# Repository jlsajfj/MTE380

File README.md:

# MTE380
STM32 Programming with NUCLEO-F401RE Board

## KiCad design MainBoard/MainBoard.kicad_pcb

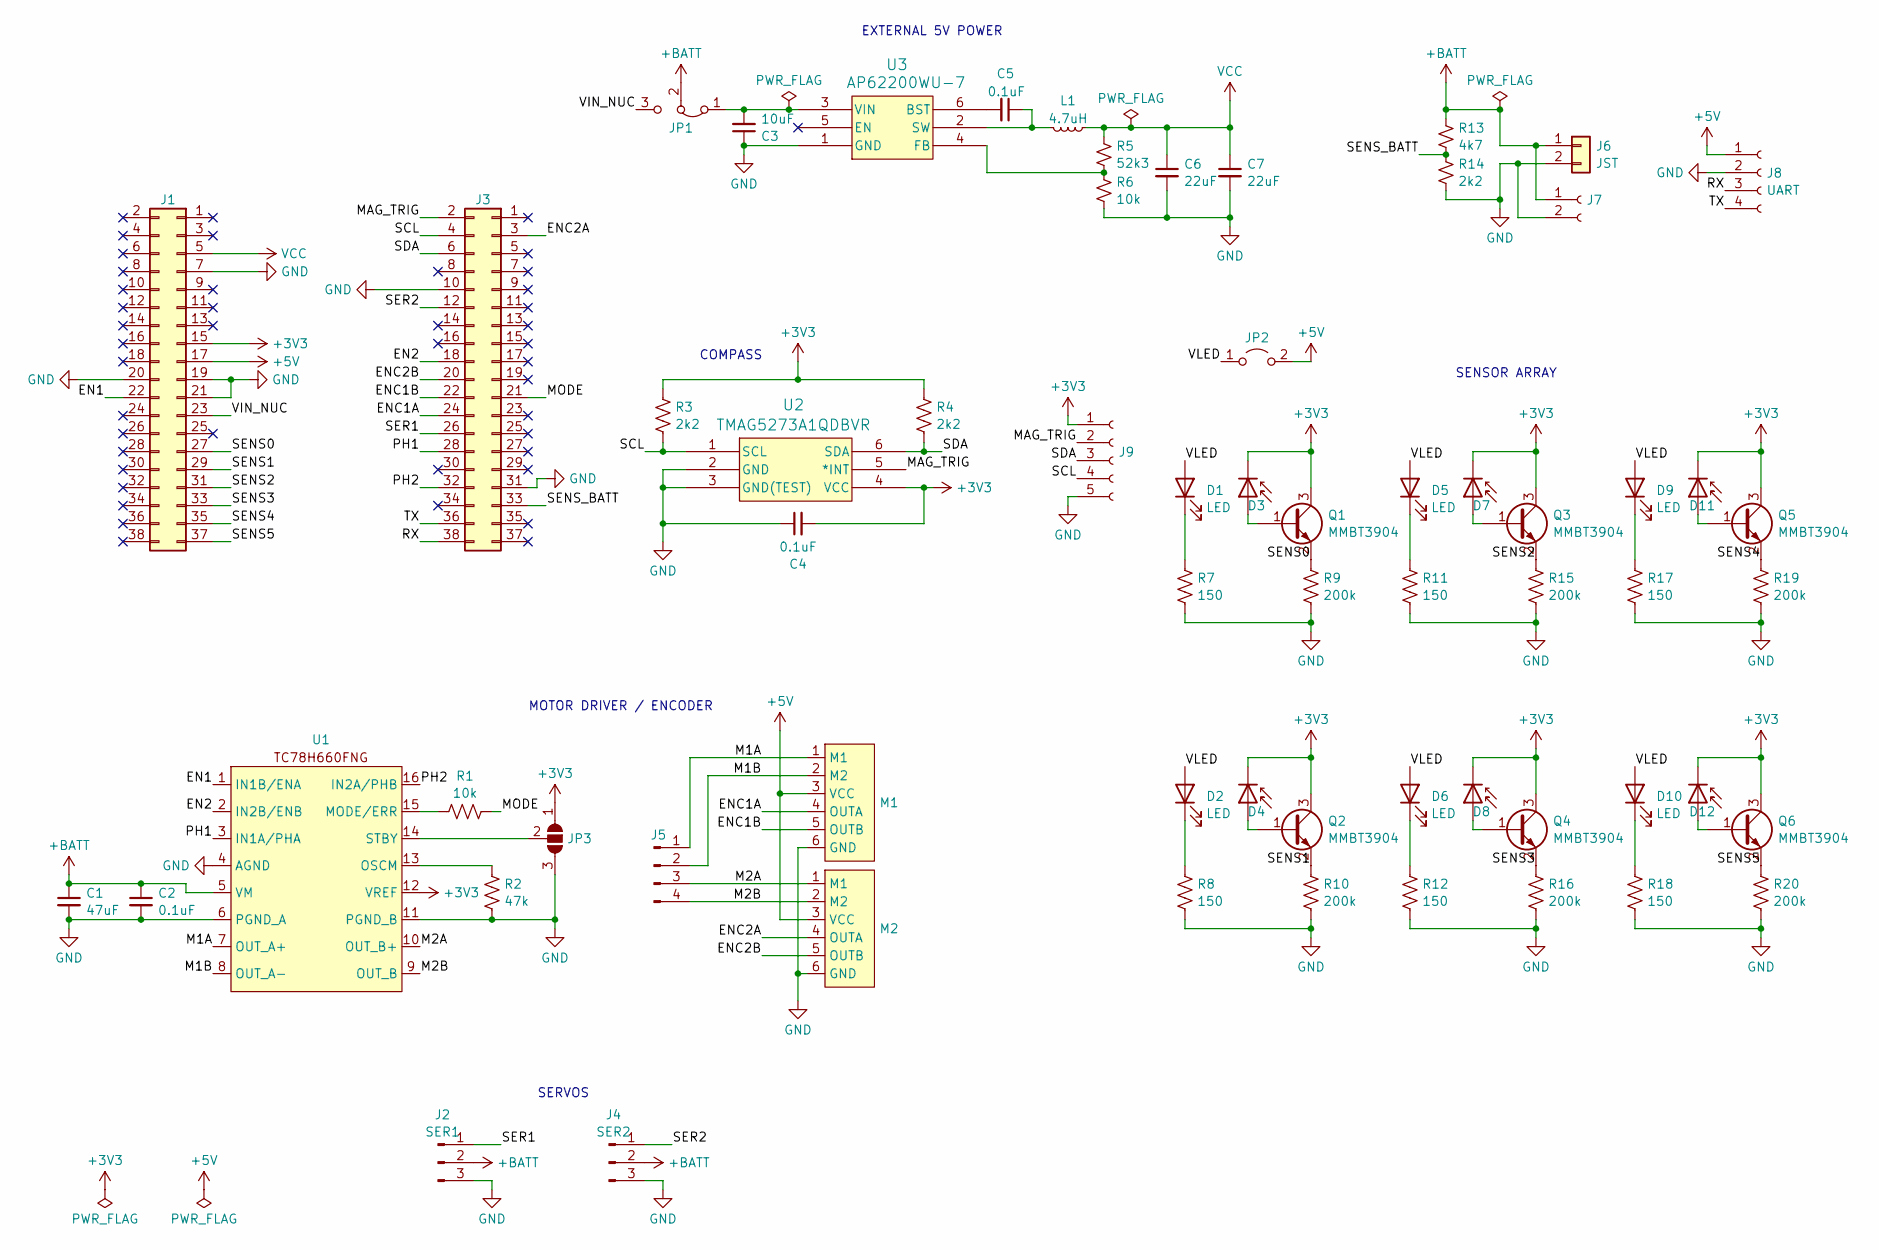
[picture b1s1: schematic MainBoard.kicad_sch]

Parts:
C1: 47uF; C_Radial_D5.0mm_H7.0mm_P2.00mm
C2, C4, C5: 0.1uF; C_0805_2012Metric_Pad1.18x1.45mm_HandSolder
C3: 10uF; C_0805_2012Metric_Pad1.18x1.45mm_HandSolder
C6, C7: 22uF; C_0805_2012Metric_Pad1.18x1.45mm_HandSolder
D1, D2, D5, D6, D9, D10: LED; LED_D3.0mm
D3, D4, D7, D8, D11, D12: D_Photo; LED_D5.0mm
J1, J3: Conn_02x19_Odd_Even; PinSocket_2x19_P2.54mm_Vertical
J2: SER1; PinHeader_1x03_P2.54mm_Vertical
J4: SER2; PinHeader_1x03_P2.54mm_Vertical
J5: Conn_01x04_Pin; PinHeader_1x04_P2.54mm_Horizontal
J6: JST; JST_PH_B2B-PH-K_1x02_P2.00mm_Vertical
J7: Conn_01x02_Socket; PinSocket_1x02_P2.54mm_Vertical
J8: UART; PinSocket_1x04_P2.54mm_Vertical
J9: Conn_01x05_Socket; PinHeader_1x05_P2.54mm_Vertical
JP1: Jumper_3_Bridged12; PinHeader_1x03_P2.54mm_Vertical
JP2: Jumper_2_Open; PinHeader_1x02_P2.54mm_Vertical
JP3: SolderJumper_3_Bridged12; SolderJumper-3_P2.0mm_Open_TrianglePad1.0x1.5mm
L1: 4.7uH; L_0805_2012Metric_Pad1.15x1.40mm_HandSolder
M1, M2: N20
Q1, Q2, Q3, Q4, Q5, Q6: MMBT3904; SOT-23_Handsoldering
R1, R6: 10k; R_0805_2012Metric_Pad1.20x1.40mm_HandSolder
R2: 47k; R_0805_2012Metric_Pad1.20x1.40mm_HandSolder
R3, R4, R14: 2k2; R_0805_2012Metric_Pad1.20x1.40mm_HandSolder
R5: 52k3; R_0805_2012Metric_Pad1.20x1.40mm_HandSolder
R7, R8, R11, R12, R17, R18: 150; R_0805_2012Metric_Pad1.20x1.40mm_HandSolder
R9, R10, R15, R16, R19, R20: 200k; R_0805_2012Metric_Pad1.20x1.40mm_HandSolder
R13: 4k7; R_0805_2012Metric_Pad1.20x1.40mm_HandSolder
U1: TSSOP-16_4.4x5mm_P0.65mm
U2: TMAG5273A1QDBVR; TSOT-23-6_HandSoldering
U3: AP62200WU-7; TSOT-23-6_HandSoldering

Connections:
+3V3: C4.2, D3.1 (K), D4.1 (K), D7.1 (K), D8.1 (K), D11.1 (K), D12.1 (K), J1.15, J9.1, JP3.1 (A), Q1.3 (C), Q2.3 (C), Q3.3 (C), Q4.3 (C), Q5.3 (C), Q6.3 (C), R3.1, R4.1, U1.12 (VREF), U2.4 (VCC)
+5V: J1.17, J8.1, JP2.2 (B), M1.3 (VCC), M2.3 (VCC)
+BATT: C1.1, C2.1, J2.2, J4.2, J6.1, J7.1, JP1.2 (C), R13.1, U1.5 (VM)
/EN1: J1.22, U1.1 (IN1B/ENA)
/EN2: J3.18, U1.2 (IN2B/ENB)
/ENC1A: J3.24, M1.4 (OUTA)
/ENC1B: J3.22, M1.5 (OUTB)
/ENC2A: J3.3, M2.4 (OUTA)
/ENC2B: J3.20, M2.5 (OUTB)
/M1A: J5.1, M1.1 (M1), U1.7 (OUT_A+)
/M1B: J5.2, M1.2 (M2), U1.8 (OUT_A-)
/M2A: J5.3, M2.1 (M1), U1.10 (OUT_B+)
/M2B: J5.4, M2.2 (M2), U1.9 (OUT_B)
/MAG_TRIG: J3.2, J9.2, U2.5 (*INT)
/MODE: J3.21, R1.2
/PH1: J3.28, U1.3 (IN1A/PHA)
/PH2: J3.32, U1.16 (IN2A/PHB)
/RX: J3.38, J8.3
/SCL: J3.4, J9.4, R3.2, U2.1 (SCL)
/SDA: J3.6, J9.3, R4.2, U2.6 (SDA)
/SENS0: J1.27, Q1.2 (E), R9.1
/SENS1: J1.29, Q2.2 (E), R10.1
/SENS2: J1.31, Q3.2 (E), R15.1
/SENS3: J1.33, Q4.2 (E), R16.1
/SENS4: J1.35, Q5.2 (E), R19.1
/SENS5: J1.37, Q6.2 (E), R20.1
/SENS_BATT: J3.33, R13.2, R14.1
/SER1: J2.1, J3.26
/SER2: J3.12, J4.1
/TX: J3.36, J8.4
/VIN_NUC: J1.23, JP1.3 (B)
/VLED: D1.2 (A), D2.2 (A), D5.2 (A), D6.2 (A), D9.2 (A), D10.2 (A), JP2.1 (A)
GND: C1.2, C2.2, C3.1, C4.1, C6.2, C7.2, J1.7, J1.19, J1.20, J1.21, J2.3, J3.10, J3.31, J4.3, J6.2, J7.2, J8.2, J9.5, JP3.3 (B), M1.6 (GND), M2.6 (GND), R2.2, R6.2, R7.2, R8.2, R9.2, R10.2, R11.2, R12.2, R14.2, R15.2, R16.2, R17.2, R18.2, R19.2, R20.2, U1.4 (AGND), U1.6 (PGND_A), U1.11 (PGND_B), U2.2 (GND), U2.3 (GND(TEST)), U3.1 (GND)
unnamed: D1.1 (K), R7.1
unnamed: D2.1 (K), R8.1
unnamed: D3.2 (A), Q1.1 (B)
unnamed: D4.2 (A), Q2.1 (B)
unnamed: D5.1 (K), R11.1
unnamed: D6.1 (K), R12.1
unnamed: D7.2 (A), Q3.1 (B)
unnamed: D8.2 (A), Q4.1 (B)
unnamed: D9.1 (K), R17.1
unnamed: D10.1 (K), R18.1
unnamed: D11.2 (A), Q5.1 (B)
unnamed: D12.2 (A), Q6.1 (B)
unnamed: C3.2, JP1.1 (A), U3.3 (VIN)
unnamed: JP3.2 (C), U1.14 (STBY)
unnamed: R1.1, U1.15 (MODE/ERR)
unnamed: R2.1, U1.13 (OSCM)
unnamed: C5.2, U3.6 (BST)
unnamed: R5.2, R6.1, U3.4 (FB)
unnamed: C5.1, L1.1, U3.2 (SW)
VCC: C6.1, C7.1, J1.5, L1.2, R5.1

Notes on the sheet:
COMPASS
EXTERNAL 5V POWER
SERVOS
MOTOR DRIVER / ENCODER
SENSOR ARRAY

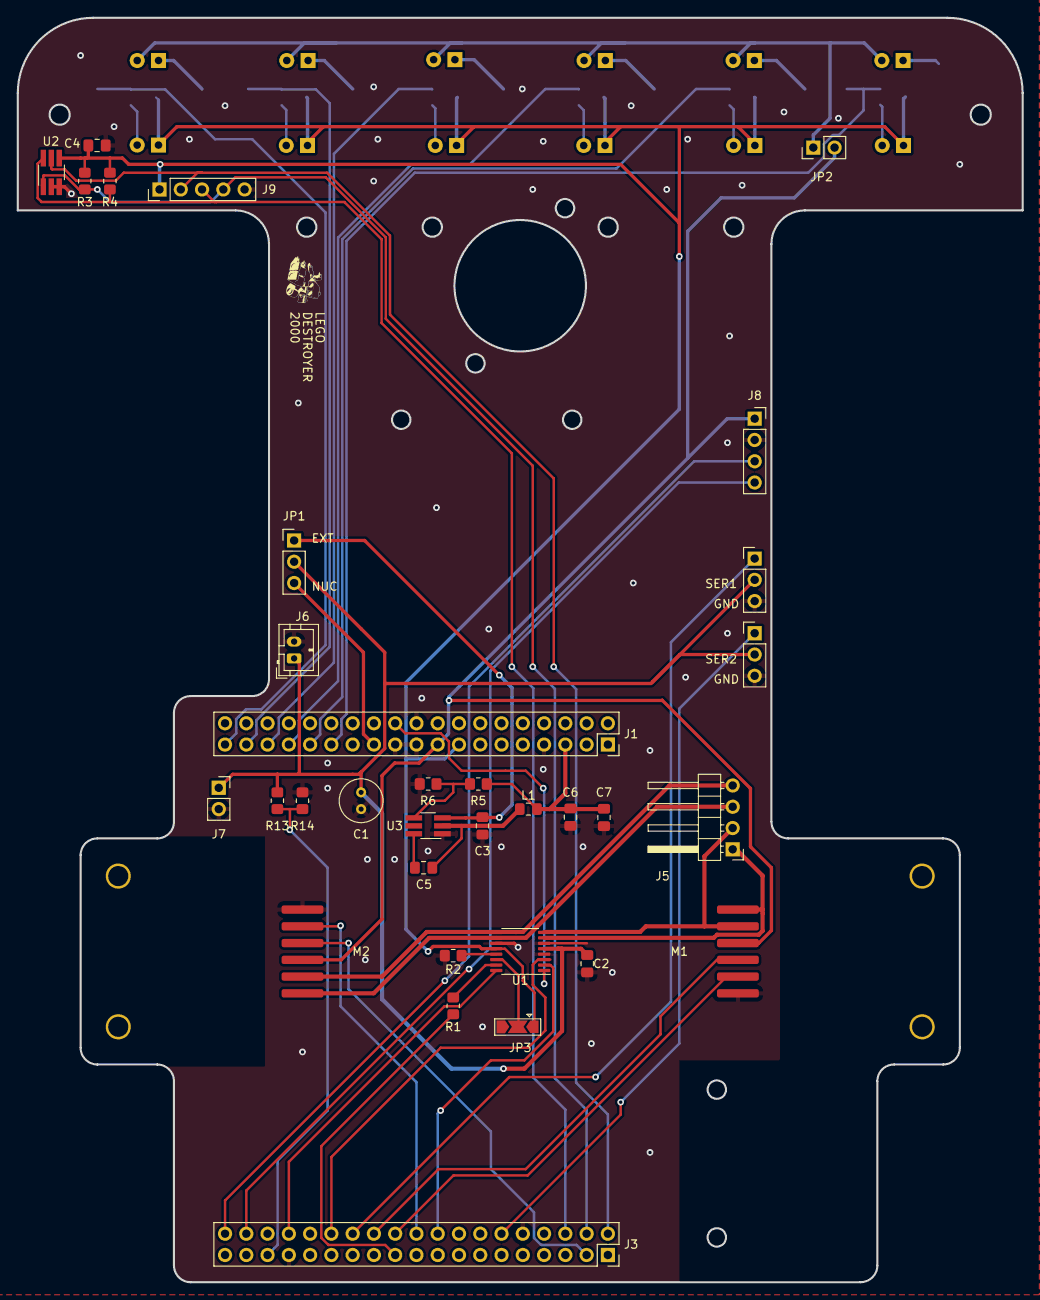
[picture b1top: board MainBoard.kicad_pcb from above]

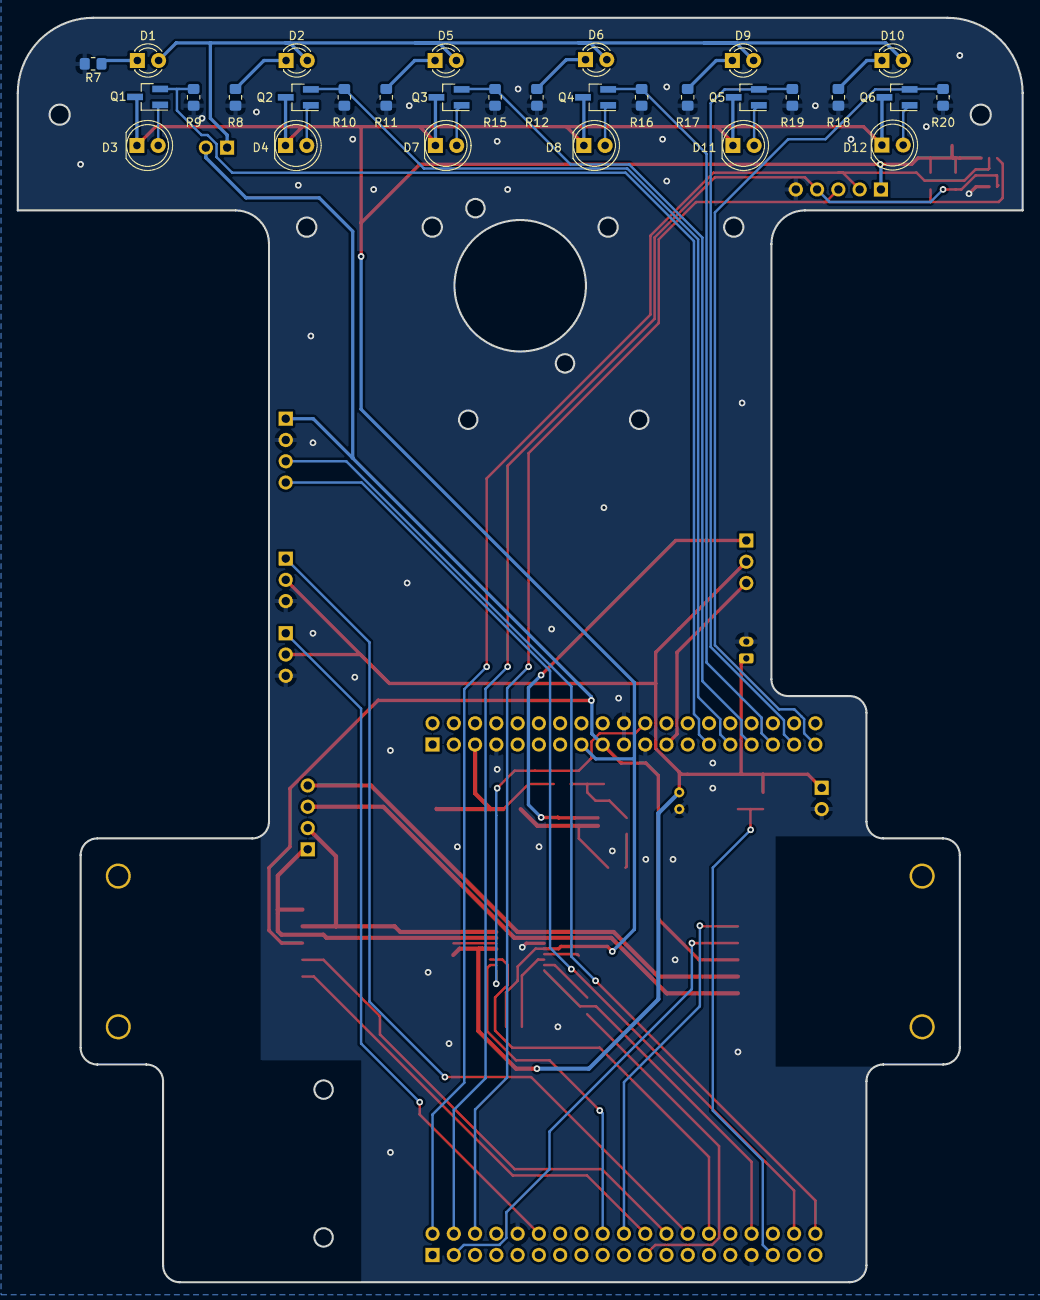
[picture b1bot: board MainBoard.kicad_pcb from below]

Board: 2 copper layers, 120.0 x 151.0 mm, 63 parts (30 on the bottom side), 53 nets.

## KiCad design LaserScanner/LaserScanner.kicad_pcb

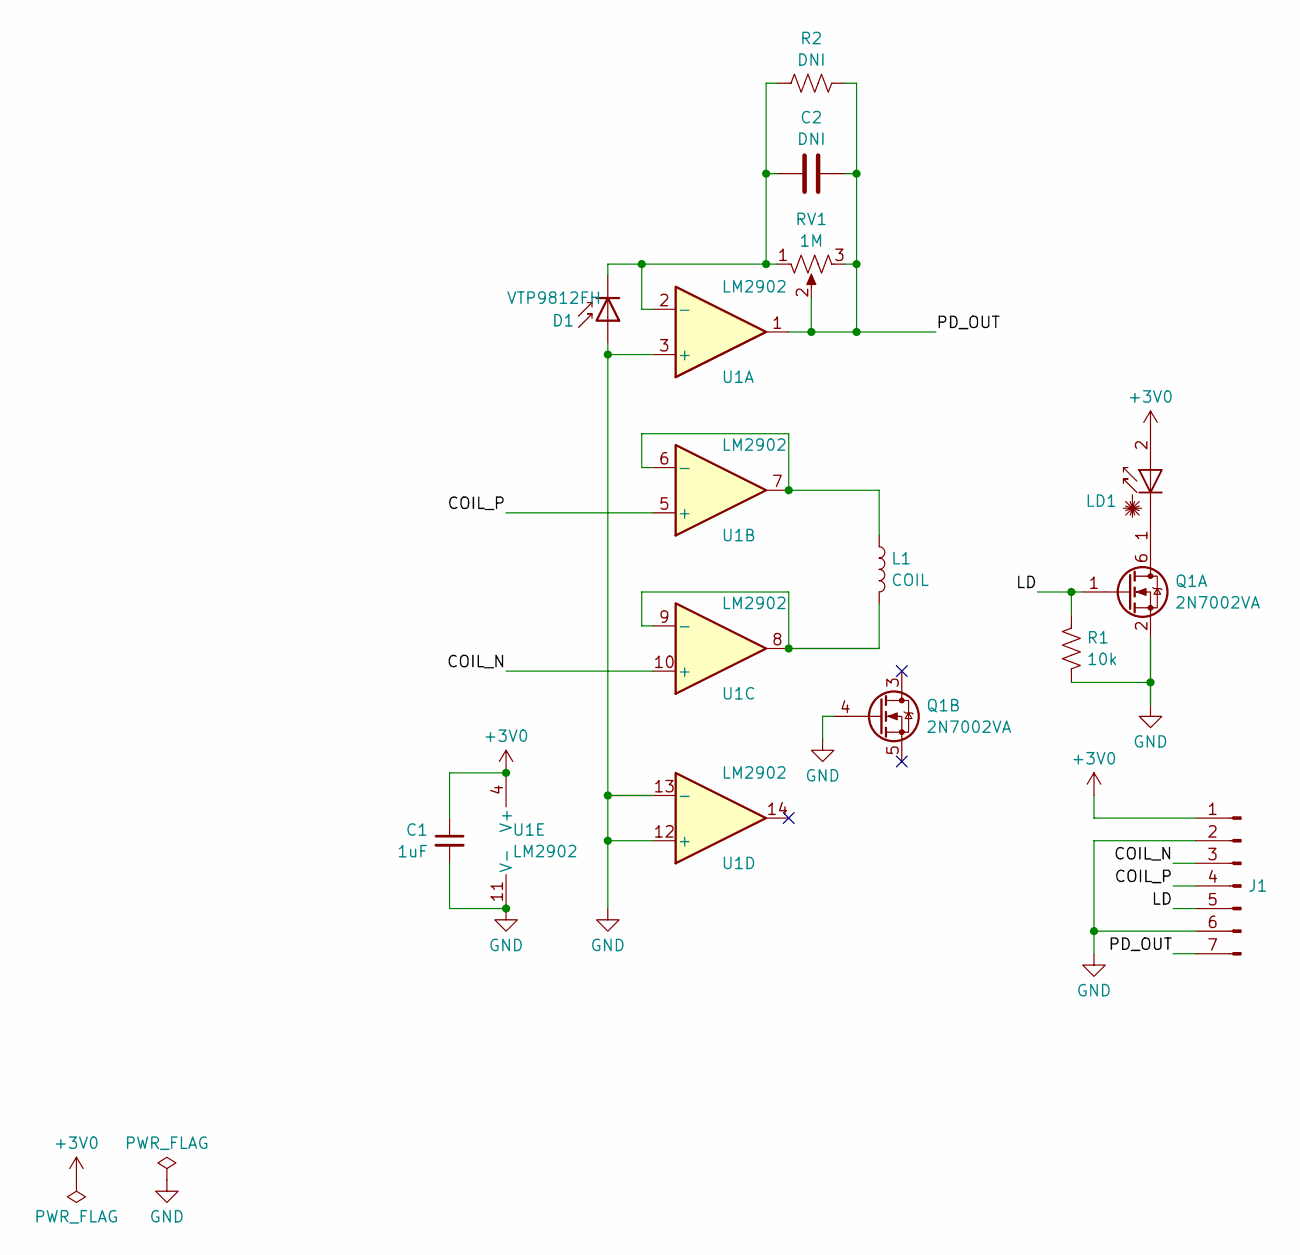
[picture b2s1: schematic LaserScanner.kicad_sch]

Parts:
C1: 1uF; C_0603_1608Metric_Pad1.08x0.95mm_HandSolder
C2: DNI; C_0603_1608Metric_Pad1.08x0.95mm_HandSolder
D1: VTP9812FH; SOD-70_P2.54mm
J1: Conn_01x06_Pin; PinHeader_1x07_P2.54mm_Horizontal
L1: COIL; PinHeader_1x02_P2.54mm_Vertical
LD1: PinHeader_1x02_P2.54mm_Vertical
Q1: 2N7002VA; SOT-23-6_Handsoldering
R1: 10k; R_0603_1608Metric_Pad0.98x0.95mm_HandSolder
R2: DNI; R_0603_1608Metric_Pad0.98x0.95mm_HandSolder
RV1: 1M; Potentiometer_Bourns_3296W_Vertical
U1: LM2902; SOIC127P600X175-14N

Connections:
+3V0: C1.1, J1.1, LD1.2 (A), U1.4 (V+)
/COIL_N: J1.3, U1.10 (+)
/COIL_P: J1.4, U1.5 (+)
/LD: J1.5, Q1.1 (G), R1.1
/PD_OUT: C2.2, J1.7, R2.2, RV1.2, RV1.3, U1.1
GND: C1.2, D1.2 (A), J1.2, J1.6, Q1.2 (S), Q1.4 (G), R1.2, U1.3 (+), U1.11 (V-), U1.12 (+), U1.13 (-)
unnamed: C2.1, D1.1 (K), R2.1, RV1.1, U1.2 (-)
unnamed: LD1.1 (K), Q1.6 (D)
unnamed: L1.1, U1.6 (-), U1.7
unnamed: L1.2, U1.8, U1.9 (-)

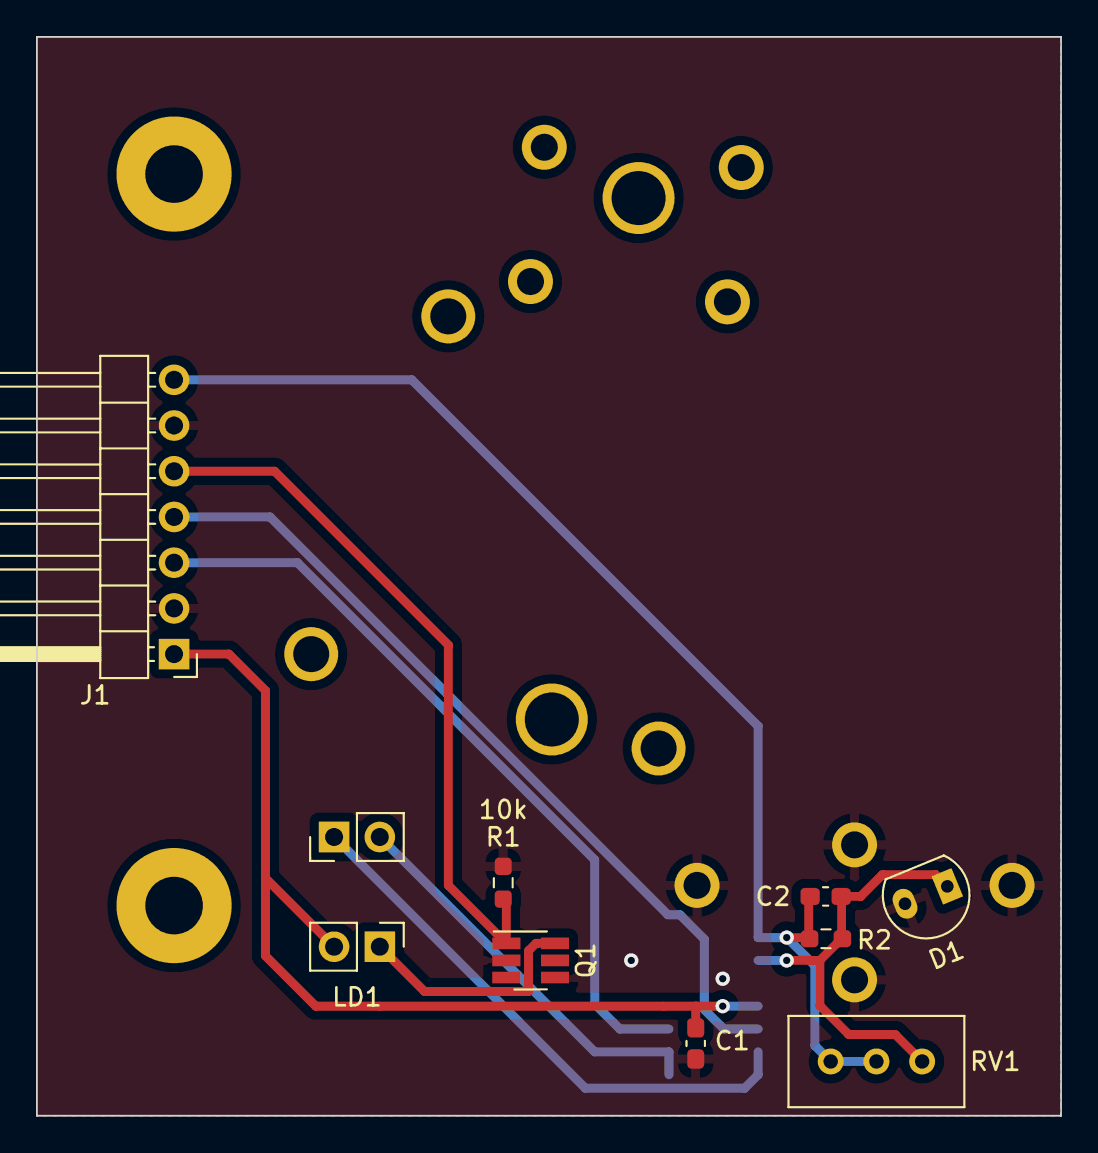
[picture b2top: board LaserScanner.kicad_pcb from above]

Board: 2 copper layers, 56.9 x 59.9 mm, 11 parts (1 on the bottom side), 10 nets.

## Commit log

2024-01-15 Project Creation
    Created Project with Nucleo-F401RE Board
2024-01-19 Motor driver first push
2024-01-20 gitignore cleanup
2024-01-20 add platformio config
2024-01-20 motor test code
2024-01-21 Motor Driver getFault and setEnabled functions
2024-01-26 adc code
2024-01-28 first line following code
2024-01-29 calibration, command system, config
2024-01-29 move more parameters to config framework
2024-01-29 make motor speed a config
2024-02-02 make sensor gains symmetric
2024-02-02 laser scanner circuit files
2024-02-02 limit speed in controller
2024-02-11 add pid controller
2024-02-11 Update Motor PWM
    change tim2 and tim3 pre-scalers. changed pre-scaler from 84 to 2, changed auto reload register from 100 to 1024
2024-02-11 Start Servo Code
    started some servo code, will need help to finish the firmware, need to add start and stop limits to command
2024-02-12 Bunch of Changes
    Updated Baud rate to 9600, created servo toggle and all other related functions
2024-02-13 experimental turn around and add servo support in commands
2024-02-15 add encoder support
2024-02-16 add pid for motor speed and position
2024-02-16 have pid_reset caller keep track of last output
2024-02-16 add interface to get motor count
2024-02-19 add compass support
2024-02-23 main board schematics
2024-02-23 add external 5V regulator
2024-02-24 use dma for serial printing
2024-02-24 bump uart rate and handle burst transmission better
2024-02-26 mainboard layout
2024-02-27 routing
2024-02-27 add logo
2024-02-27 update routing
2024-03-01 fix motor pid usage
2024-03-01 poc pid tuning tool
2024-03-06 update to new board
2024-03-07 add lowpass to compass calibration; add demo code
2024-03-08 add multi servo support
2024-03-10 battery voltage; add idle mode to compass
2024-03-12 elliptic curve compass calibration
2024-03-13 add a higher level state machine
2024-03-13 update schematics datasheet link
2024-03-13 populate state machine
2024-03-14 add stable margin as pid config
    clean up command parsing
    experiment variable speed control
2024-03-14 working course with preset speed points
2024-03-14 update state machine
2024-03-14 add arcing
2024-03-15 start server
2024-03-15 framework for connection
2024-03-16 add binary telemetry
2024-03-16 gui serial communication poc
2024-03-16 no need for control in position/arc/turn mode
2024-03-17 add nack
2024-03-17 added NACK + black
2024-03-17 dict for stream
2024-03-18 course speed training
2024-03-19 starting backend threading
2024-03-19 moving away archive of crappy code
2024-03-20 improve speed recording
2024-03-20 fix new speed record; update states
2024-03-20 music
2024-03-21 add encoder steps to target detection
2024-03-21 basic graph for single wheel
2024-03-21 improvements to page
2024-03-21 send back commands
2024-03-21 site v1
2024-03-21 styling changes + additional functionality
2024-03-22 code updates
2024-03-22 rename to server
2024-03-22 black
2024-03-22 flake fixes
2024-03-22 icecream music
2024-03-22 fix motor pwm output; change telemetry sync
2024-03-23 remove getting
2024-03-23 use states to decode packets; improve firmware uart
2024-03-23 add button to clear charts
2024-03-23 move state to property, remove synced boolean
2024-03-23 add ack return, run black formatter
2024-03-23 remove unnecessary time
2024-03-23 ack print
2024-03-23 add color ack/nack for site
2024-03-23 add typing and introduce helper class for Filters
2024-03-23 fix serial command reading
2024-03-23 fix command ack/nack
2024-03-23 plot both wheels in tuner.py
2024-03-24 add slip factor to speed control encoder count
2024-03-24 better button behaviour
2024-03-25 dump config after set
2024-03-25 add config viewer and updater
2024-03-25 Overall Front-End Update
    + beginning map code
    + reorganize front-end
    + add navigation
2024-03-25 add start of map
2024-03-26 fix map code
2024-03-26 map improvements
2024-03-26 config update map update
2024-03-26 music selector
2024-03-26 update to front end
2024-03-26 add line on map
2024-03-26 modularise path
2024-03-26 return speed points with get
2024-03-26 adding path tracer
2024-03-26 start mobile site
2024-03-28 only start tone timer when playing
2024-03-28 change arc and turn stop condition; update states
2024-03-28 remove music commands, it burns the motor
2024-03-28 removing music
2024-03-28 better record and target dertection; update tuner script ui
2024-03-29 unnormalize sensor weight
2024-03-29 isort/black
2024-03-29 change to enum
2024-03-30 fix python enum comparison
2024-03-30 enum change
2024-03-30 fix tuner
2024-03-31 add align command and sensor latching
2024-04-01 icon
2024-04-01 add arrow key changes
2024-04-01 improve line following
2024-04-02 update state machine and have seprate config for arc turn push speed
2024-04-02 save working config
2024-04-03 flipped motor
2024-04-03 switch to software pwm as walkaround for fried gpio pin
2024-04-04 update config and fix server
2024-04-05 Lets burn the motor
    This reverts commit 16ad9728e0c84d04c44268af0af05d88e351d093.
